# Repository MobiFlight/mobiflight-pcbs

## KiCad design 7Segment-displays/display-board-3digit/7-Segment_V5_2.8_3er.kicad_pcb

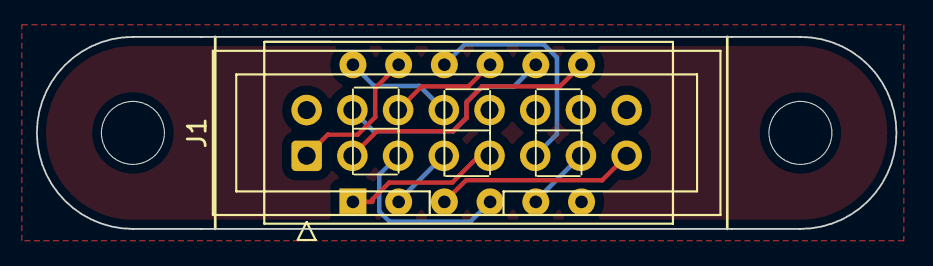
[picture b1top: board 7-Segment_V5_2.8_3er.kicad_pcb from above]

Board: 2 copper layers, 47.8 x 10.7 mm, 5 parts (1 on the bottom side), 11 nets.

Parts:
G2: LOGO; MobiFlight1
J1: Conn_02x08_Odd_Even; IDC-Header_2x08_P2.54mm_Vertical
REF1: MountingHole_3.5mm1; MountingHole_3.5mm
REF2: MountingHole_3.5mm2; MountingHole_3.5mm
U1: 7Segment 3 digit common cathode STH; STH_7_3 Digits_0.28_CC

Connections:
/A: J1.1, U1.11 (a)
/B: J1.3, U1.7 (b)
/C: J1.5, U1.4 (c)
/D: J1.7, U1.2 (d)
/DIG0: J1.4, U1.8 (CC3)
/DIG1: J1.6, U1.9 (CC2)
/DIG2: J1.8, U1.12 (CC1)
/DP: J1.15, U1.3 (DPX)
/E: J1.9, U1.1 (e)
/F: J1.11, U1.10 (f)
/G: J1.13, U1.5 (g)

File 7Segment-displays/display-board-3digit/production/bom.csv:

Designator,Footprint,Quantity,Value,LCSC Part #
J1,IDC-Header_2x08_P2.54mm_Vertical,1,Conn_02x08_Odd_Even,
U1,STH_7_3 Digits_0.28_CC,1,7Segment 3 digit common cathode STH,

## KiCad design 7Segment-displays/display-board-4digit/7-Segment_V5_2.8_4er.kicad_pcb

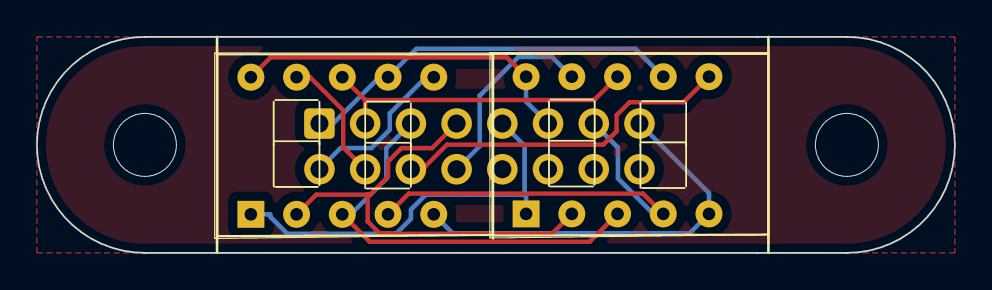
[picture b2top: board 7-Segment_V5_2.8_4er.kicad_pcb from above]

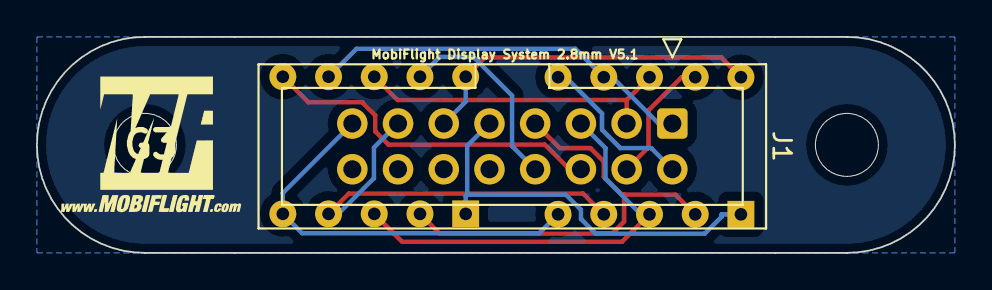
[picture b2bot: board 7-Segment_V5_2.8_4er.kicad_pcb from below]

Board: 2 copper layers, 51.0 x 12.0 mm, 6 parts (2 on the bottom side), 12 nets.

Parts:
G3: LOGO; MobiFlight1
J1: Conn_02x08_Odd_Even; IDC-Header_2x08_P2.54mm_Vertical
REF1, REF2: MountingHole_3.5mm
U1, U2: HDSM-443B_CC_2Digit_7Segment_STH; STH_7_2 Digits_0.28_CC

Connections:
/A: J1.1, U1.7 (A), U2.7 (A)
/B: J1.3, U1.8 (B), U2.8 (B)
/C: J1.5, U1.3 (C), U2.3 (C)
/D: J1.7, U1.2 (D), U2.2 (D)
/DIG0: J1.2, U2.6 (CC_DIG2)
/DIG1: J1.4, U2.9 (CC_DIG1)
/DIG2: J1.6, U1.6 (CC_DIG2)
/DIG3: J1.8, U1.9 (CC_DIG1)
/DP: J1.15, U1.5 (DP), U2.5 (DP)
/E: J1.9, U1.1 (E), U2.1 (E)
/F: J1.11, U1.10 (F), U2.10 (F)
/G: J1.13, U1.4 (G), U2.4 (G)

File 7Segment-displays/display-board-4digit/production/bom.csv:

Designator,Footprint,Quantity,Value,LCSC Part #
J1,IDC-Header_2x08_P2.54mm_Vertical,1,Conn_02x08_Odd_Even,
"U1, U2",STH_7_2 Digits_0.28_CC,2,HDSM-443B_CC_2Digit_7Segment_STH,

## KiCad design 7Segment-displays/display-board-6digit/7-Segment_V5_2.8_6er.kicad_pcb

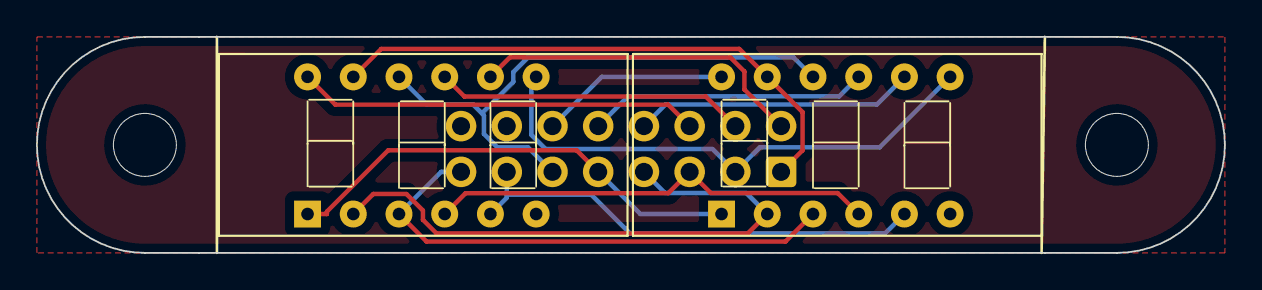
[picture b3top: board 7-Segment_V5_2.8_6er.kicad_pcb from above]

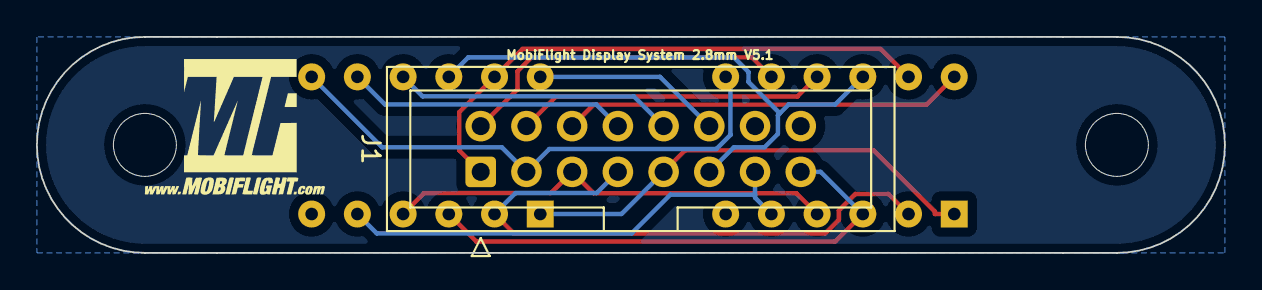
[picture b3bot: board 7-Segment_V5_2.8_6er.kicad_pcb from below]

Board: 2 copper layers, 66.0 x 12.0 mm, 6 parts (2 on the bottom side), 14 nets.

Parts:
G3: LOGO; MobiFlight1
J1: Conn_02x08_Odd_Even; IDC-Header_2x08_P2.54mm_Vertical
REF1, REF2: MountingHole_3.5mm
U1, U2: 7Segment 3 digit CC_STH; STH_7_3 Digits_0.28_CC

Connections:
/A: J1.1, U1.11 (a), U2.11 (a)
/B: J1.3, U1.7 (b), U2.7 (b)
/C: J1.5, U1.4 (c), U2.4 (c)
/D: J1.7, U1.2 (d), U2.2 (d)
/DIG0: J1.2, U2.8 (CC3)
/DIG1: J1.4, U2.9 (CC2)
/DIG2: J1.6, U2.12 (CC1)
/DIG3: J1.8, U1.8 (CC3)
/DIG4: J1.10, U1.9 (CC2)
/DIG5: J1.12, U1.12 (CC1)
/DP: J1.15, U1.3 (DPX), U2.3 (DPX)
/E: J1.9, U1.1 (e), U2.1 (e)
/F: J1.11, U1.10 (f), U2.10 (f)
/G: J1.13, U1.5 (g), U2.5 (g)

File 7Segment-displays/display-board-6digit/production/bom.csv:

Designator,Footprint,Quantity,Value,LCSC Part #
J1,IDC-Header_2x08_P2.54mm_Vertical,1,Conn_02x08_Odd_Even,
"U1, U2",STH_7_3 Digits_0.28_CC,2,7Segment 3 digit CC_STH,

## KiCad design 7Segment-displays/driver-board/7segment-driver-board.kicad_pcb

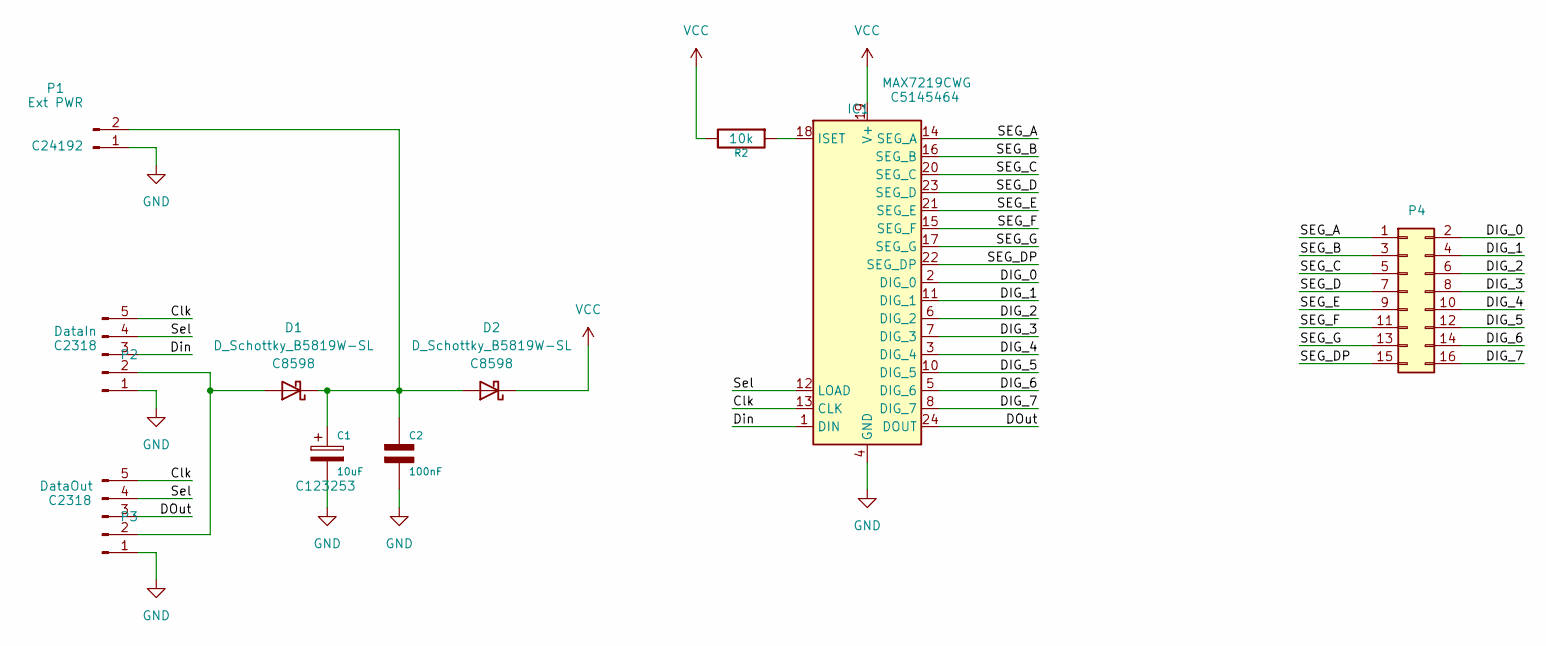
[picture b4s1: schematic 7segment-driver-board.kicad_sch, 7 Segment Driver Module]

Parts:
C1: 10uF; CP_EIA-3528-21_Kemet-B; LCSC C123253
C2: 100nF; C_0603_1608Metric; LCSC C14663
D1, D2: D_Schottky_B5819W-SL; D_SOD-123; LCSC C8598
IC1: MAX7219CWG; SOIC-24W_7.5x15.4mm_P1.27mm; LCSC C5145464
P1: Ext PWR; JST_XH_B2B-XH-A_1x02_P2.50mm_Vertical; LCSC C24192
P2: DataIn; JST_XH_B5B-XH-A_1x05_P2.50mm_Vertical; LCSC C2318
P3: DataOut; JST_XH_B5B-XH-A_1x05_P2.50mm_Vertical; LCSC C2318
P4: Display; PinSocket_2x08_P2.54mm_Vertical_SMD
R2: 10k; R_0603_1608Metric; LCSC C25804

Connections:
/Clk: IC1.13 (CLK), P2.5, P3.5
/DIG_0: IC1.2 (DIG_0), P4.2
/DIG_1: IC1.11 (DIG_1), P4.4
/DIG_2: IC1.6 (DIG_2), P4.6
/DIG_3: IC1.7 (DIG_3), P4.8
/DIG_4: IC1.3 (DIG_4), P4.10
/DIG_5: IC1.10 (DIG_5), P4.12
/DIG_6: IC1.5 (DIG_6), P4.14
/DIG_7: IC1.8 (DIG_7), P4.16
/DOut: IC1.24 (DOUT), P3.3
/Din: IC1.1 (DIN), P2.3
/SEG_A: IC1.14 (SEG_A), P4.1
/SEG_B: IC1.16 (SEG_B), P4.3
/SEG_C: IC1.20 (SEG_C), P4.5
/SEG_D: IC1.23 (SEG_D), P4.7
/SEG_DP: IC1.22 (SEG_DP), P4.15
/SEG_E: IC1.21 (SEG_E), P4.9
/SEG_F: IC1.15 (SEG_F), P4.11
/SEG_G: IC1.17 (SEG_G), P4.13
/Sel: IC1.12 (LOAD), P2.4, P3.4
GND: C1.2, C2.2, IC1.4 (GND), IC1.9 (GND), P1.1, P2.1, P3.1
unnamed: D1.2 (A), P2.2, P3.2
unnamed: C1.1, C2.1, D1.1 (K), D2.2 (A), P1.2
unnamed: IC1.18 (ISET), R2.1
VCC: D2.1 (K), IC1.19 (V+), R2.2

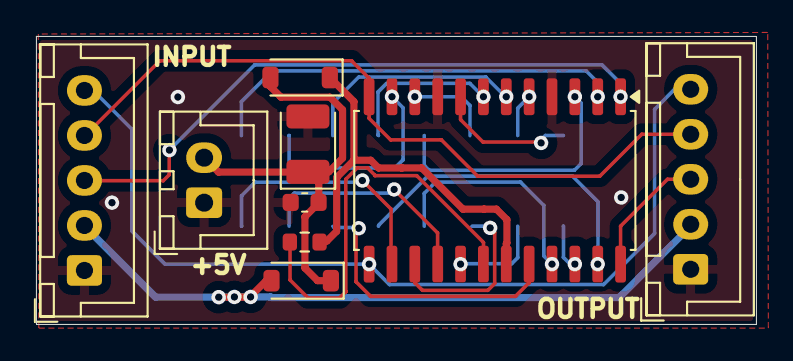
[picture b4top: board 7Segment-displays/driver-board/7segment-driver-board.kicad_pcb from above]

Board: 2 copper layers, 40.0 x 16.0 mm, 10 parts (1 on the bottom side), 25 nets.

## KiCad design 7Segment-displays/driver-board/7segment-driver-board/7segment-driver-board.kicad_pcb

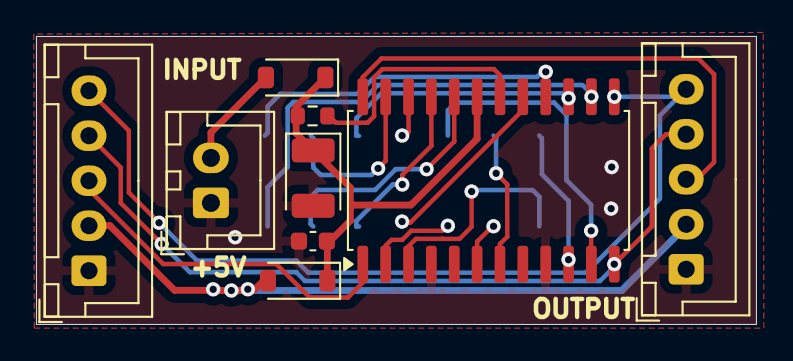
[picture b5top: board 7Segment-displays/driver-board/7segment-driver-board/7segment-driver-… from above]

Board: 2 copper layers, 40.0 x 16.0 mm, 10 parts (1 on the bottom side), 23 nets.

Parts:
C1: 10uF; CP_EIA-3528-21_Kemet-B
C2: 100nF; C_0603_1608Metric
D1, D2: D_Schottky_B5819W-SL; D_SOD-123
IC1: MAX7219CWG; SOIC-24W_7.5x15.4mm_P1.27mm
P1: Ext PWR; JST_XH_B2B-XH-A_1x02_P2.50mm_Vertical
P2: DataIn; JST_XH_B5B-XH-A_1x05_P2.50mm_Vertical
P3: DataOut; JST_XH_B5B-XH-A_1x05_P2.50mm_Vertical
P4: D0-D5; PinSocket_2x07_P2.54mm_Vertical_SMD
R2: 22k; R_0603_1608Metric

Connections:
/Clk: IC1.13 (CLK), P2.5, P3.5
/DIG_0: IC1.2 (DIG_0), P4.9
/DIG_1: IC1.11 (DIG_1), P4.10
/DIG_2: IC1.6 (DIG_2), P4.11
/DIG_3: IC1.7 (DIG_3), P4.12
/DIG_4: IC1.3 (DIG_4), P4.13
/DIG_5: IC1.10 (DIG_5), P4.14
/DOut: IC1.24 (DOUT), P3.3
/Din: IC1.1 (DIN), P2.3
/SEG_A: IC1.14 (SEG_A), P4.1
/SEG_B: IC1.16 (SEG_B), P4.2
/SEG_C: IC1.20 (SEG_C), P4.3
/SEG_D: IC1.23 (SEG_D), P4.4
/SEG_DP: IC1.22 (SEG_DP), P4.8
/SEG_E: IC1.21 (SEG_E), P4.5
/SEG_F: IC1.15 (SEG_F), P4.6
/SEG_G: IC1.17 (SEG_G), P4.7
/Sel: IC1.12 (LOAD), P2.4, P3.4
GND: C1.2, C2.2, IC1.4 (GND), IC1.9 (GND), P1.1, P2.1, P3.1
unnamed: D1.2 (A), P2.2, P3.2
unnamed: D2.2 (A), P1.2
unnamed: IC1.18 (ISET), R2.1
VCC: C1.1, C2.1, D1.1 (K), D2.1 (K), IC1.19 (V+), R2.2

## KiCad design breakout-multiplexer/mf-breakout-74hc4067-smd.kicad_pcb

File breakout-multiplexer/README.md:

# MobiFlight Multiplexer Breakout Board
The MobiFlight Multiplexer Breakout Board is a breakout board for easier use of the 74HC4067 multiplexer. It is designed to work best together with the [MobiFlight Prototyping Board](https://shop.mobiflight.com/product/prototyping-board-v2).

On the top side, The board uses XH JST connectors for the individual inputs.

From Version 1.2 now shows information about the orientation and all important pins are labeled.
You can daisy chain the boards.

For more information on how to configure the board with MobiFlight, check out the [MobiFlight Connector documentation](https://github.com/MobiFlight/MobiFlight-Connector/wiki/Input-and-Output-devices#input-multiplexer).

## Board overview

### Multiplexer IN
Connection coming from your Mobiflight board, or another MobiFlight Multiplexer Breakout Board as daisy chain.

* Pin1 - GND
* Pin2 - VCC
* Pin3 - Channel 1
* Pin4 - Channel 2
* Pin5 - Channel 3
* Pin6 - Channel 4

### Data
Connection coming from your Mobiflight board.

* Pin1 - GND
* Pin2 - Signal pin (for the first 74HC4067)
* Pin3 - Signal pin (for the second 74HC4067)

### Multiplexer OUT
Connection to daisy chain another MobiFlight Multiplexer Breakout Board.

* Pin1 - GND
* Pin2 - VCC
* Pin3 - Channel 1
* Pin4 - Channel 2
* Pin5 - Channel 3
* Pin6 - Channel 4

### Button01-08
First row of connectors for input devices buttons and switches:

* Pin1 - Connection TO switch
* Pin2 - Connection FROM switch

Polarity doesn't matter for switches.

### Button09-16
Second row of connectors for input devices buttons and switches:

* Pin1 - Connection TO switch
* Pin2 - Connection FROM switch

Polarity doesn't matter for switches.

### Button 17-24
First row of connectors for input devices buttons and switches:

* Pin1 - Connection TO switch
* Pin2 - Connection FROM switch

Polarity doesn't matter for switches.

### Button 25-32
Second row of connectors for input devices buttons and switches:

* Pin1 - Connection TO switch
* Pin2 - Connection FROM switch

Polarity doesn't matter for switches.

## Connecting and wiring
The multiplexer prototyping board is designed to work best together with the [MobiFlight Prototyping Board](https://shop.mobiflight.com/product/prototyping-board-v2). Of course, you can also connect it directly to any of the supported microcontrollers.

### MobiFlight Prototyping Board
The prototyping board comes with the required cables to make connection super easy.

* **Connect the 6-pin wire** from the breakout board to the MobiFlight Prototyping Board's 6-pin connector labeled **Stepper 2 / Multiplexer**
* **Connect the 3-pin wires** to the MobiFlight Prototyping Board's 3-pin connectors **Switch 6** respectively
* **Upload multiplexer board configuration** to the MobiFlight Prototyping Board - [Download multiplexer-config (mfmc)](https://raw.githubusercontent.com/MobiFlight/mobiflight-pcbs/refs/heads/main/prototyping-board/prototyping-board.multiplexer.mfmc)

All pins on the multiplexer will now work correctly!

### Direct connection
If you are using any of the supported microcontrollers, do the following:

#### Wiring
* Connect the first two pins on the **Multiplexer In** connector to **GND**, **5V** and the four remaining pins to free output-capable pins. For an Arduino Mega that could be, eg. D2, D3 D4 and D5. 
* Connect the input-capable pins to Data connectors - first pin is **GND** and is not necessarily required, second pin is data 0 and third pin is data 1 pins. You can verify by looking on the backside of the circuit board where the pins are labeled. 

#### Board configuration
You should first add one multiplexer device with the four data pins configured as follows, and select also the pin connected to Data0. Data1 will be assigned to a another Multiplexer device we add after this one.

For the second multiplexer add another multiplexer device from the menu, the four selector pins will be the same, and the **data pin** will a unique one for the second multiplexer, D7 for example.

Click "Upload config" and your device should work.

## MobiFlight Configuration

> This information will be added soon.

## Case
You can print a case for the board [using this STL file](breakout-multiplexer-case.stl) for better handling and look:

## Additional information

### Bottom side

### Schematic

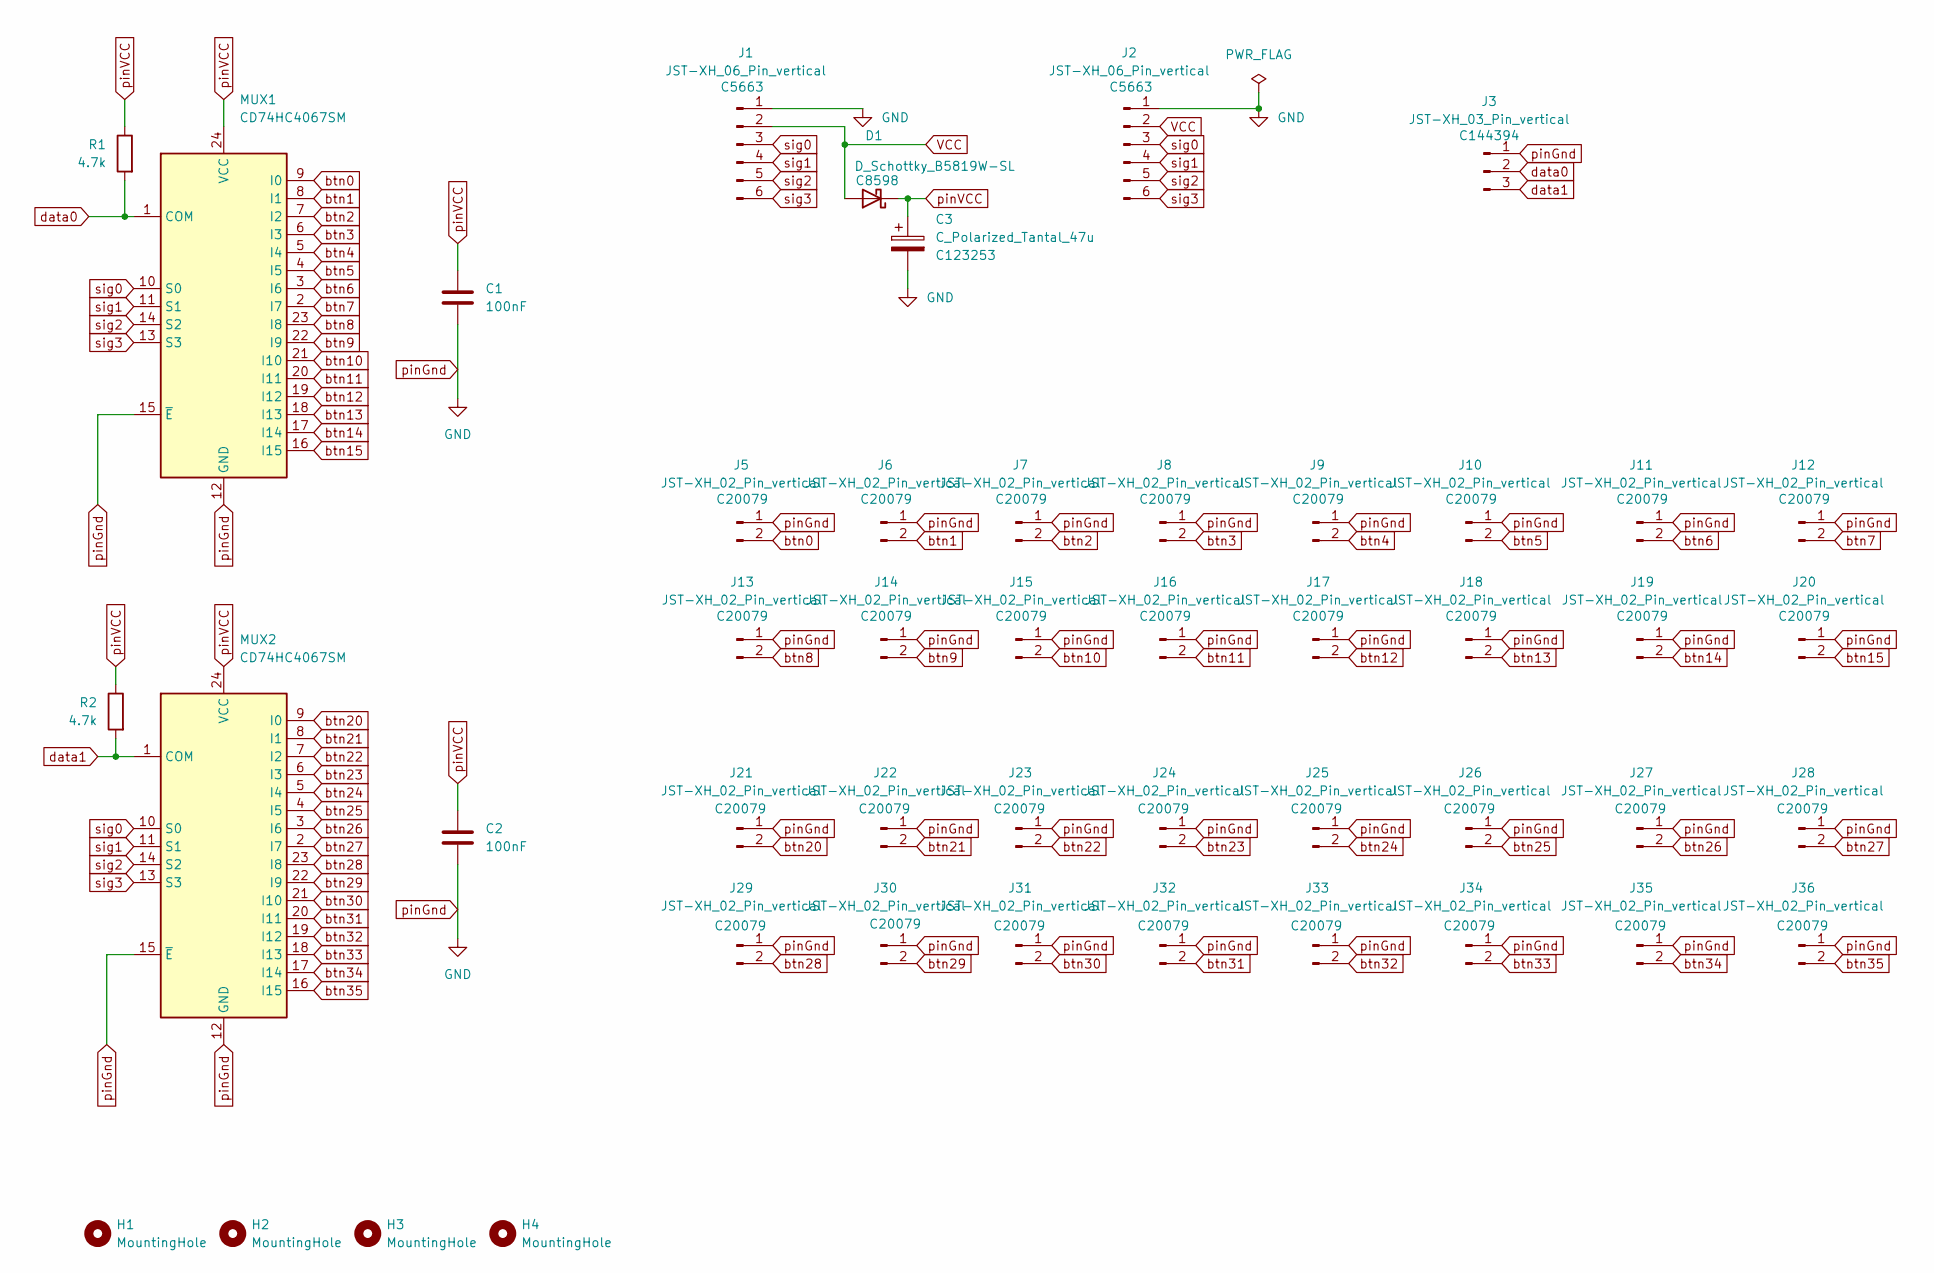
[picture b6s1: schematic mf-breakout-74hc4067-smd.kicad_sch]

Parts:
C1, C2: 100nF; C_0805_2012Metric; LCSC C28233
C3: C_Polarized_Tantal_47u; CP_EIA-3528-21_Kemet-B; LCSC C123253
D1: D_Schottky_B5819W-SL; D_SOD-123; LCSC C8598
H1, H2, H3, H4: MountingHole; MountingHole_3.5mm_Pad
J1, J2: JST-XH_06_Pin_vertical; JST_XH_B6B-XH-A_1x06_P2.50mm_Vertical; JLC Rotation Offset 0
J3: JST-XH_03_Pin_vertical; JST_XH_B3B-XH-A_1x03_P2.50mm_Vertical; LCSC C144394
J5, J6, J7, J8, J9, J10, J11, J12, J13, J14, J15, J16, J17, J18, J19, J20, J21, J22, J23, J24, J25, J26, J27, J28, J29, J30, J31, J32, J33, J34, J35, J36: JST-XH_02_Pin_vertical; JST_XH_B2B-XH-A_1x02_P2.50mm_Vertical; JLC Rotation Offset 180
MUX1, MUX2: CD74HC4067SM; SSOP-24_5.3x8.2mm_P0.65mm; LCSC C98457
R1, R2: 4.7k; R_0805_2012Metric; LCSC C17673

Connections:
VCC: D1.2 (A), J1.2, J2.2
btn0: J5.2, MUX1.9 (I0)
btn1: J6.2, MUX1.8 (I1)
btn2: J7.2, MUX1.7 (I2)
btn3: J8.2, MUX1.6 (I3)
btn4: J9.2, MUX1.5 (I4)
btn5: J10.2, MUX1.4 (I5)
btn6: J11.2, MUX1.3 (I6)
btn7: J12.2, MUX1.2 (I7)
btn8: J13.2, MUX1.23 (I8)
btn9: J14.2, MUX1.22 (I9)
btn10: J15.2, MUX1.21 (I10)
btn11: J16.2, MUX1.20 (I11)
btn12: J17.2, MUX1.19 (I12)
btn13: J18.2, MUX1.18 (I13)
btn14: J19.2, MUX1.17 (I14)
btn15: J20.2, MUX1.16 (I15)
btn20: J21.2, MUX2.9 (I0)
btn21: J22.2, MUX2.8 (I1)
btn22: J23.2, MUX2.7 (I2)
btn23: J24.2, MUX2.6 (I3)
btn24: J25.2, MUX2.5 (I4)
btn25: J26.2, MUX2.4 (I5)
btn26: J27.2, MUX2.3 (I6)
btn27: J28.2, MUX2.2 (I7)
btn28: J29.2, MUX2.23 (I8)
btn29: J30.2, MUX2.22 (I9)
btn30: J31.2, MUX2.21 (I10)
btn31: J32.2, MUX2.20 (I11)
btn32: J33.2, MUX2.19 (I12)
btn33: J34.2, MUX2.18 (I13)
btn34: J35.2, MUX2.17 (I14)
btn35: J36.2, MUX2.16 (I15)
data0: J3.2, MUX1.1 (COM), R1.2
data1: J3.3, MUX2.1 (COM), R2.2
pinGnd: C1.2, C2.2, C3.2, J1.1, J2.1, J3.1, J5.1, J6.1, J7.1, J8.1, J9.1, J10.1, J11.1, J12.1, J13.1, J14.1, J15.1, J16.1, J17.1, J18.1, J19.1, J20.1, J21.1, J22.1, J23.1, J24.1, J25.1, J26.1, J27.1, J28.1, J29.1, J30.1, J31.1, J32.1, J33.1, J34.1, J35.1, J36.1, MUX1.12 (GND), MUX1.15 (~E), MUX2.12 (GND), MUX2.15 (~E)
pinVCC: C1.1, C2.1, C3.1, D1.1 (K), MUX1.24 (VCC), MUX2.24 (VCC), R1.1, R2.1
sig0: J1.3, J2.3, MUX1.10 (S0), MUX2.10 (S0)
sig1: J1.4, J2.4, MUX1.11 (S1), MUX2.11 (S1)
sig2: J1.5, J2.5, MUX1.14 (S2), MUX2.14 (S2)
sig3: J1.6, J2.6, MUX1.13 (S3), MUX2.13 (S3)

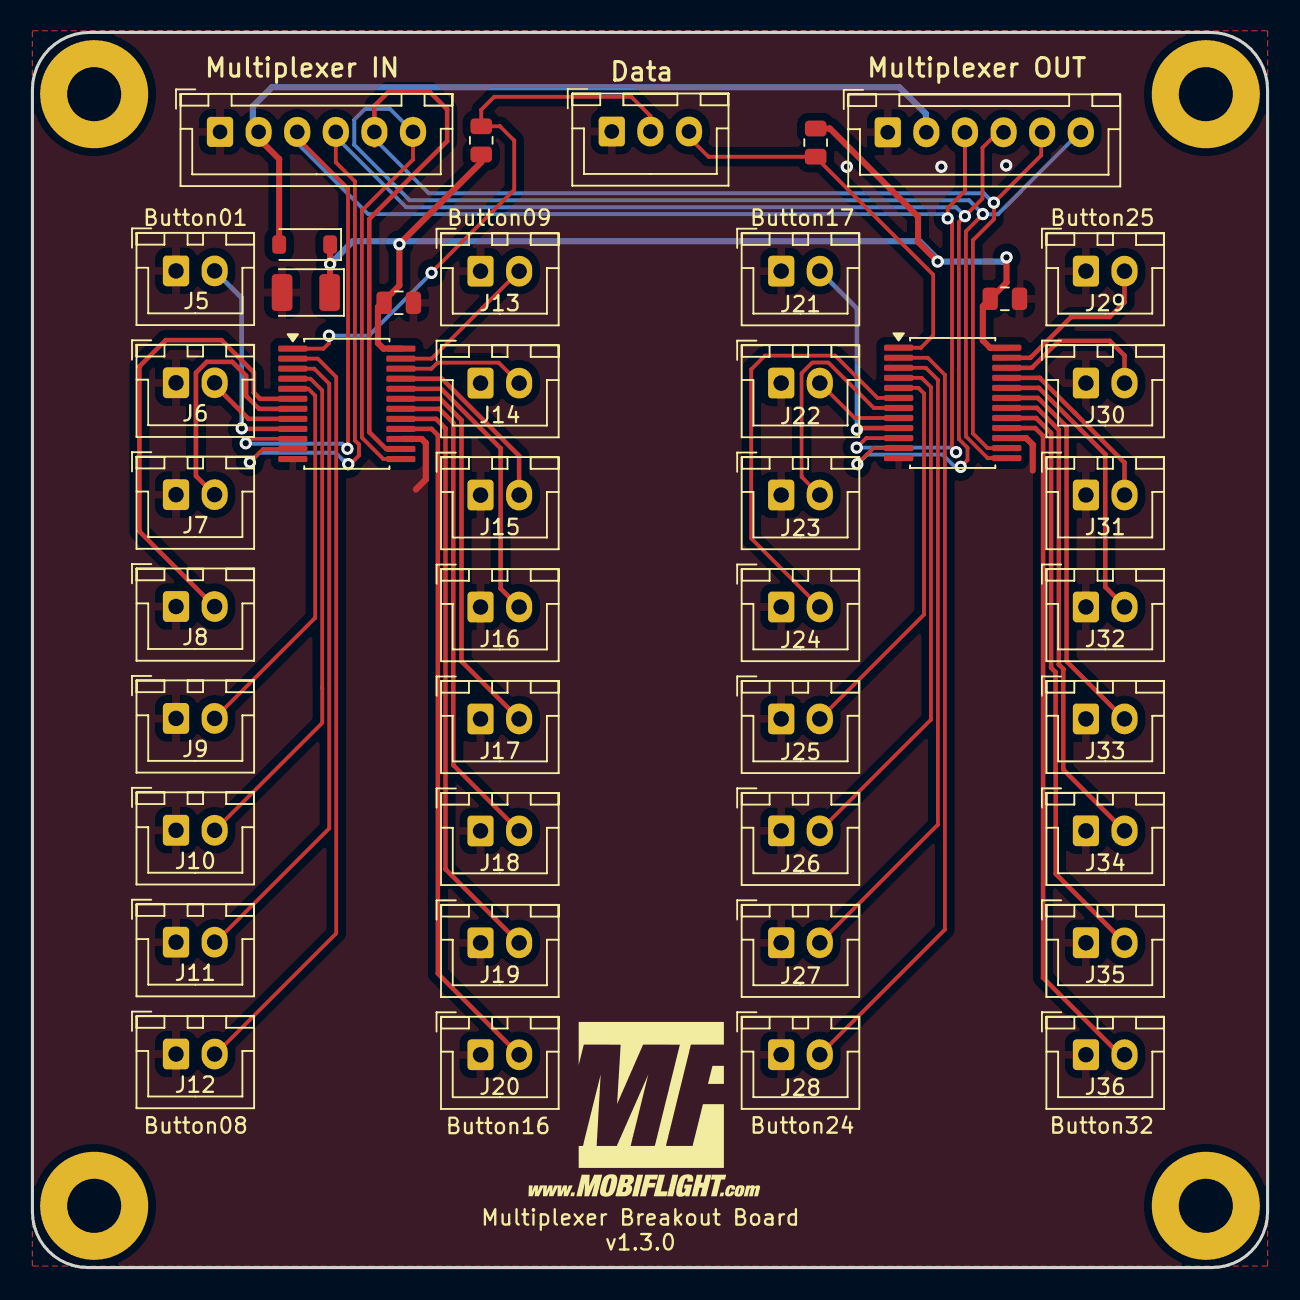
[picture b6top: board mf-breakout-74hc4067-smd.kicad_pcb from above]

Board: 2 copper layers, 80.0 x 80.0 mm, 47 parts (0 on the bottom side), 41 nets.

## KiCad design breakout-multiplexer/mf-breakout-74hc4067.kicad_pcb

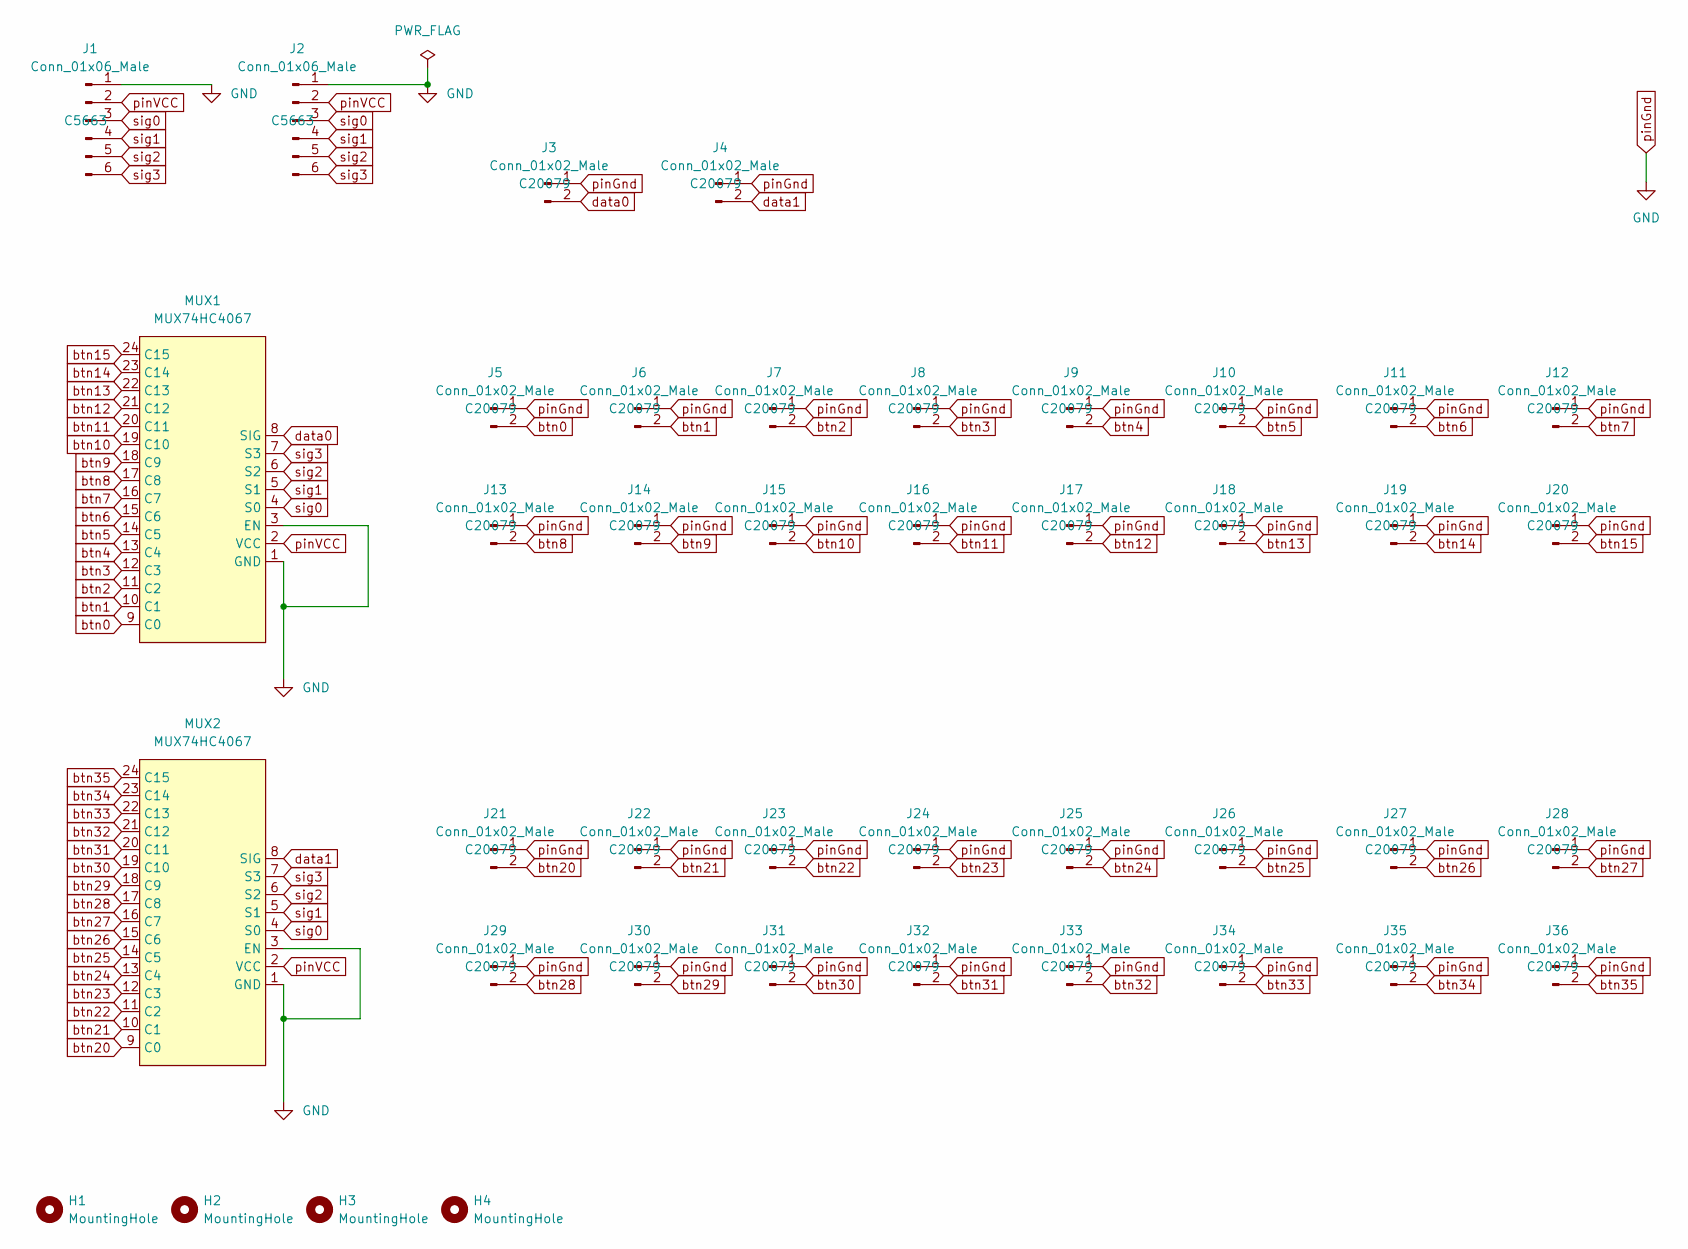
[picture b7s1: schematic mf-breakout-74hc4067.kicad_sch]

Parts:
H1, H2, H3, H4: MountingHole; MountingHole_3.5mm_Pad
J1, J2: Conn_01x06_Male; JST_XH_B6B-XH-A_1x06_P2.50mm_Vertical; MPN C5663; JLC Rotation Offset 0
J3, J4, J5, J6, J7, J8, J9, J10, J11, J12, J13, J14, J15, J16, J17, J18, J19, J20, J21, J22, J23, J24, J25, J26, J27, J28, J29, J30, J31, J32, J33, J34, J35, J36: Conn_01x02_Male; JST_XH_B2B-XH-A_1x02_P2.50mm_Vertical; MPN C20079; JLC Rotation Offset 180
MUX1, MUX2: MUX74HC4067; 74HC4067

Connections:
btn0: J5.2, MUX1.9 (C0)
btn1: J6.2, MUX1.10 (C1)
btn2: J7.2, MUX1.11 (C2)
btn3: J8.2, MUX1.12 (C3)
btn4: J9.2, MUX1.13 (C4)
btn5: J10.2, MUX1.14 (C5)
btn6: J11.2, MUX1.15 (C6)
btn7: J12.2, MUX1.16 (C7)
btn8: J13.2, MUX1.17 (C8)
btn9: J14.2, MUX1.18 (C9)
btn10: J15.2, MUX1.19 (C10)
btn11: J16.2, MUX1.20 (C11)
btn12: J17.2, MUX1.21 (C12)
btn13: J18.2, MUX1.22 (C13)
btn14: J19.2, MUX1.23 (C14)
btn15: J20.2, MUX1.24 (C15)
btn20: J21.2, MUX2.9 (C0)
btn21: J22.2, MUX2.10 (C1)
btn22: J23.2, MUX2.11 (C2)
btn23: J24.2, MUX2.12 (C3)
btn24: J25.2, MUX2.13 (C4)
btn25: J26.2, MUX2.14 (C5)
btn26: J27.2, MUX2.15 (C6)
btn27: J28.2, MUX2.16 (C7)
btn28: J29.2, MUX2.17 (C8)
btn29: J30.2, MUX2.18 (C9)
btn30: J31.2, MUX2.19 (C10)
btn31: J32.2, MUX2.20 (C11)
btn32: J33.2, MUX2.21 (C12)
btn33: J34.2, MUX2.22 (C13)
btn34: J35.2, MUX2.23 (C14)
btn35: J36.2, MUX2.24 (C15)
data0: J3.2, MUX1.8 (SIG)
data1: J4.2, MUX2.8 (SIG)
pinGnd: J1.1, J2.1, J3.1, J4.1, J5.1, J6.1, J7.1, J8.1, J9.1, J10.1, J11.1, J12.1, J13.1, J14.1, J15.1, J16.1, J17.1, J18.1, J19.1, J20.1, J21.1, J22.1, J23.1, J24.1, J25.1, J26.1, J27.1, J28.1, J29.1, J30.1, J31.1, J32.1, J33.1, J34.1, J35.1, J36.1, MUX1.1 (GND), MUX1.3 (EN), MUX2.1 (GND), MUX2.3 (EN)
pinVCC: J1.2, J2.2, MUX1.2 (VCC), MUX2.2 (VCC)
sig0: J1.3, J2.3, MUX1.4 (S0), MUX2.4 (S0)
sig1: J1.4, J2.4, MUX1.5 (S1), MUX2.5 (S1)
sig2: J1.5, J2.5, MUX1.6 (S2), MUX2.6 (S2)
sig3: J1.6, J2.6, MUX1.7 (S3), MUX2.7 (S3)

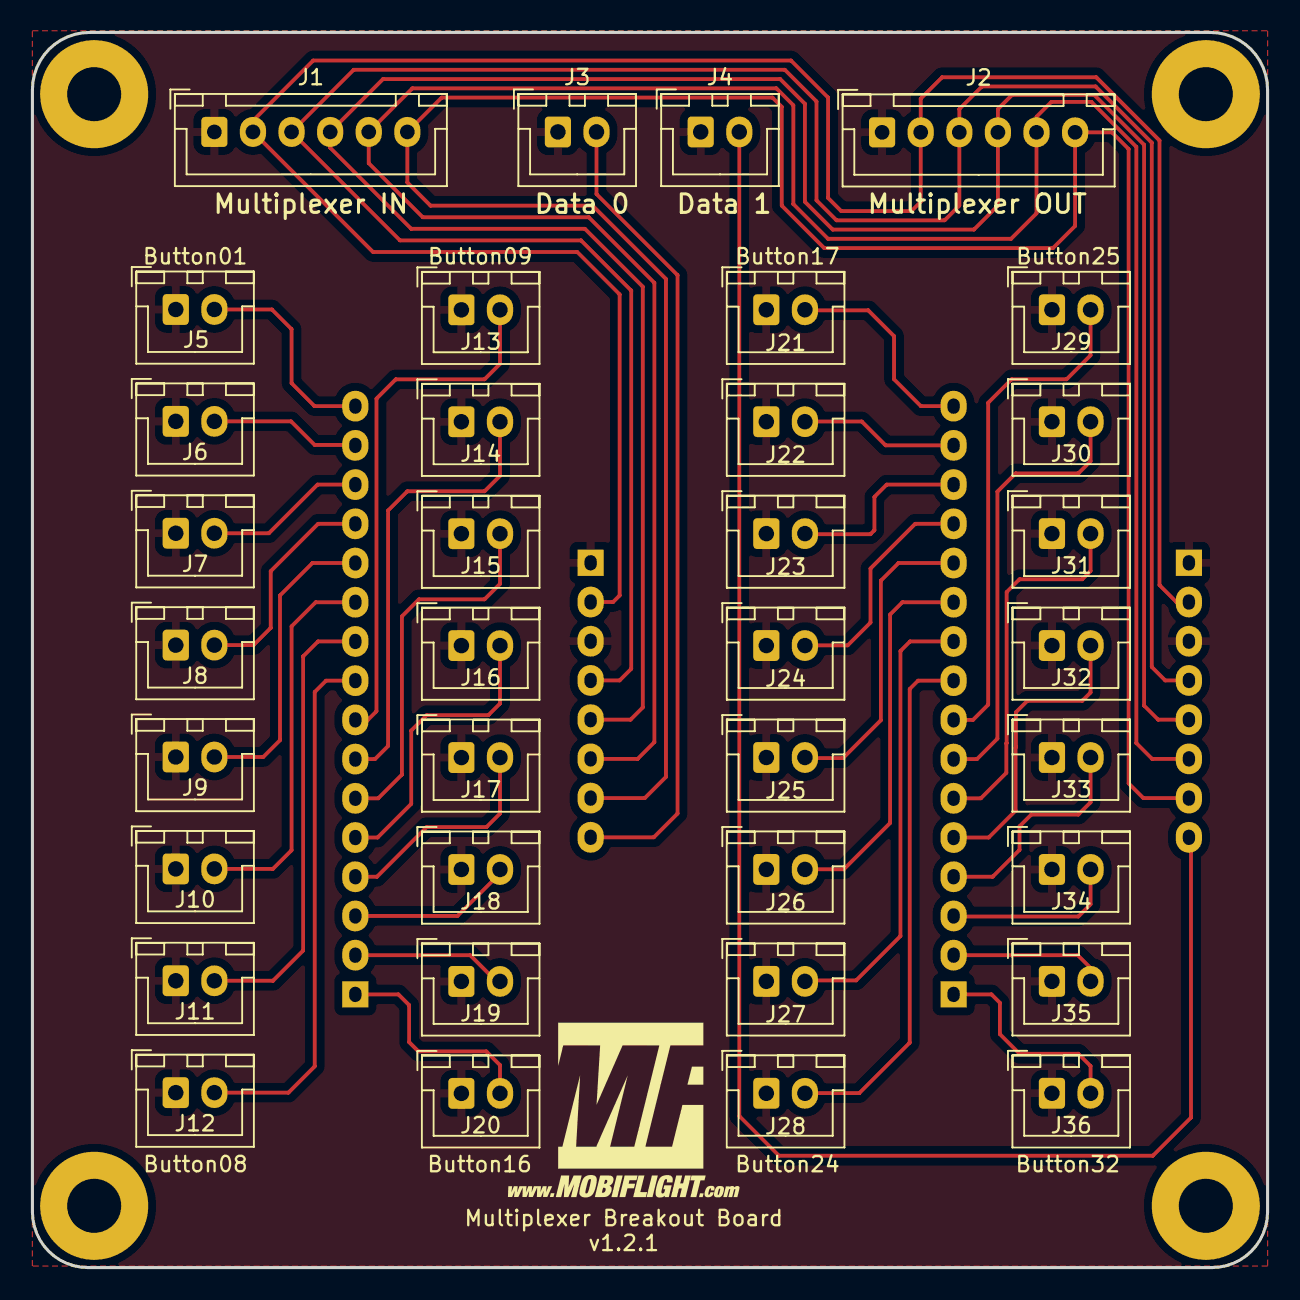
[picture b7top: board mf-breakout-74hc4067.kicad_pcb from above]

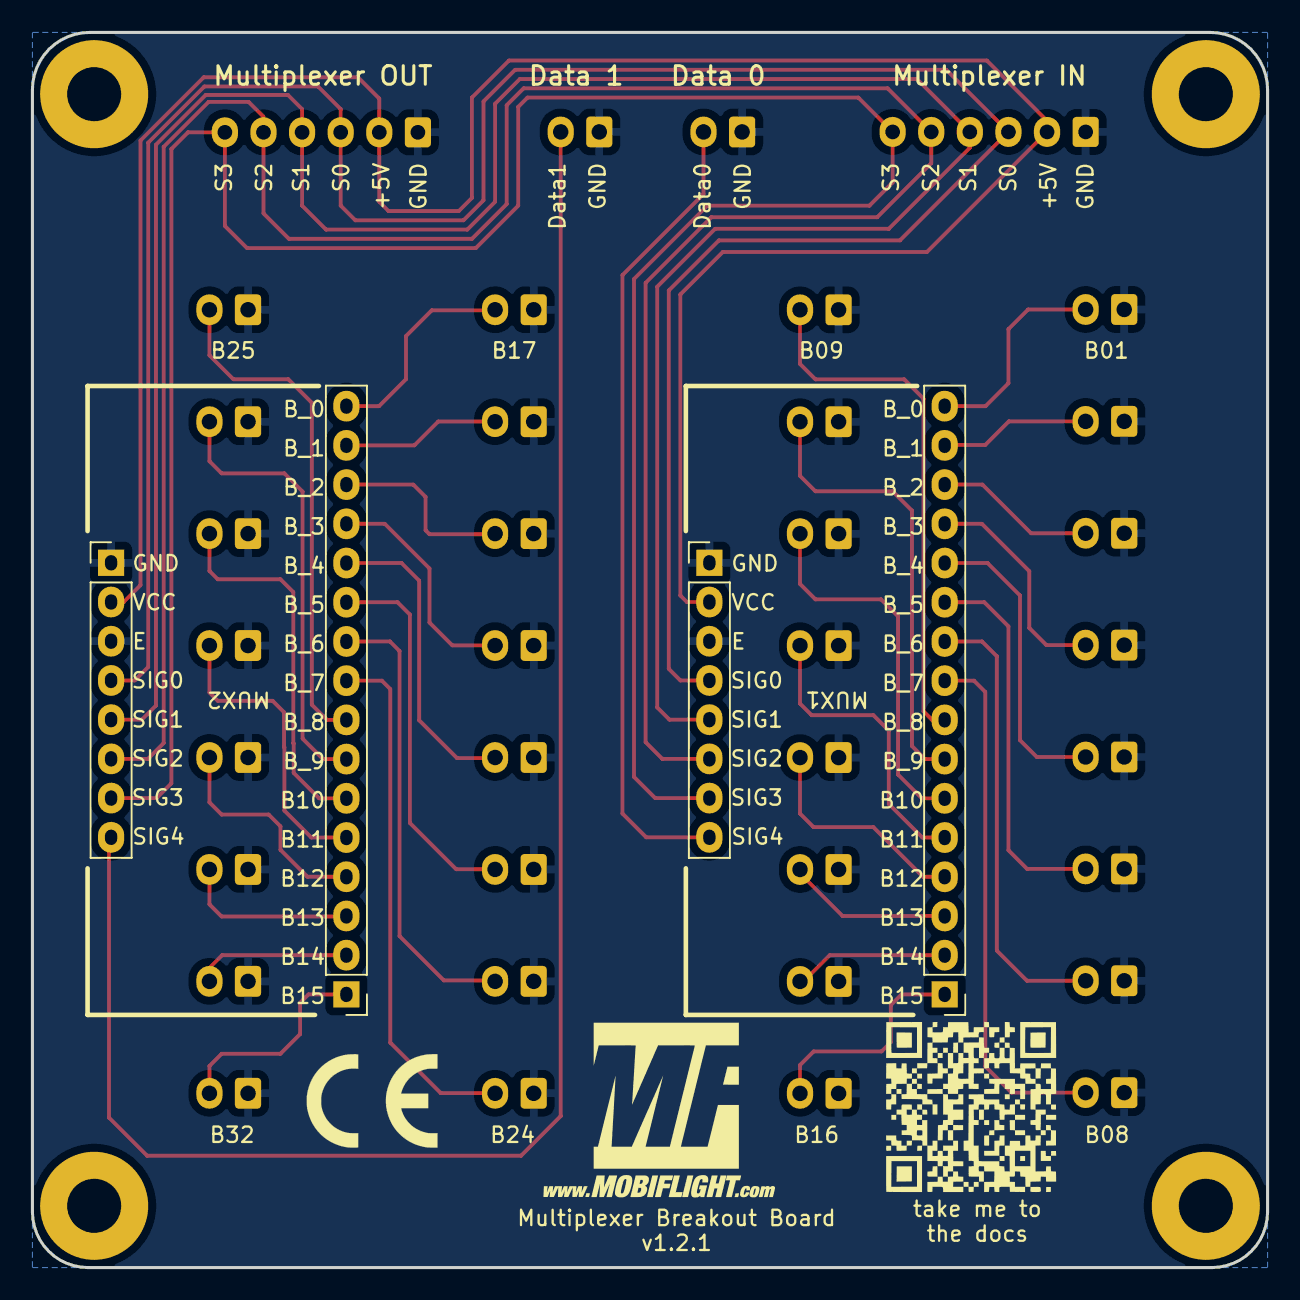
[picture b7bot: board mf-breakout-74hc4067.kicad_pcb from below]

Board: 2 copper layers, 80.0 x 80.0 mm, 42 parts (2 on the bottom side), 40 nets.
